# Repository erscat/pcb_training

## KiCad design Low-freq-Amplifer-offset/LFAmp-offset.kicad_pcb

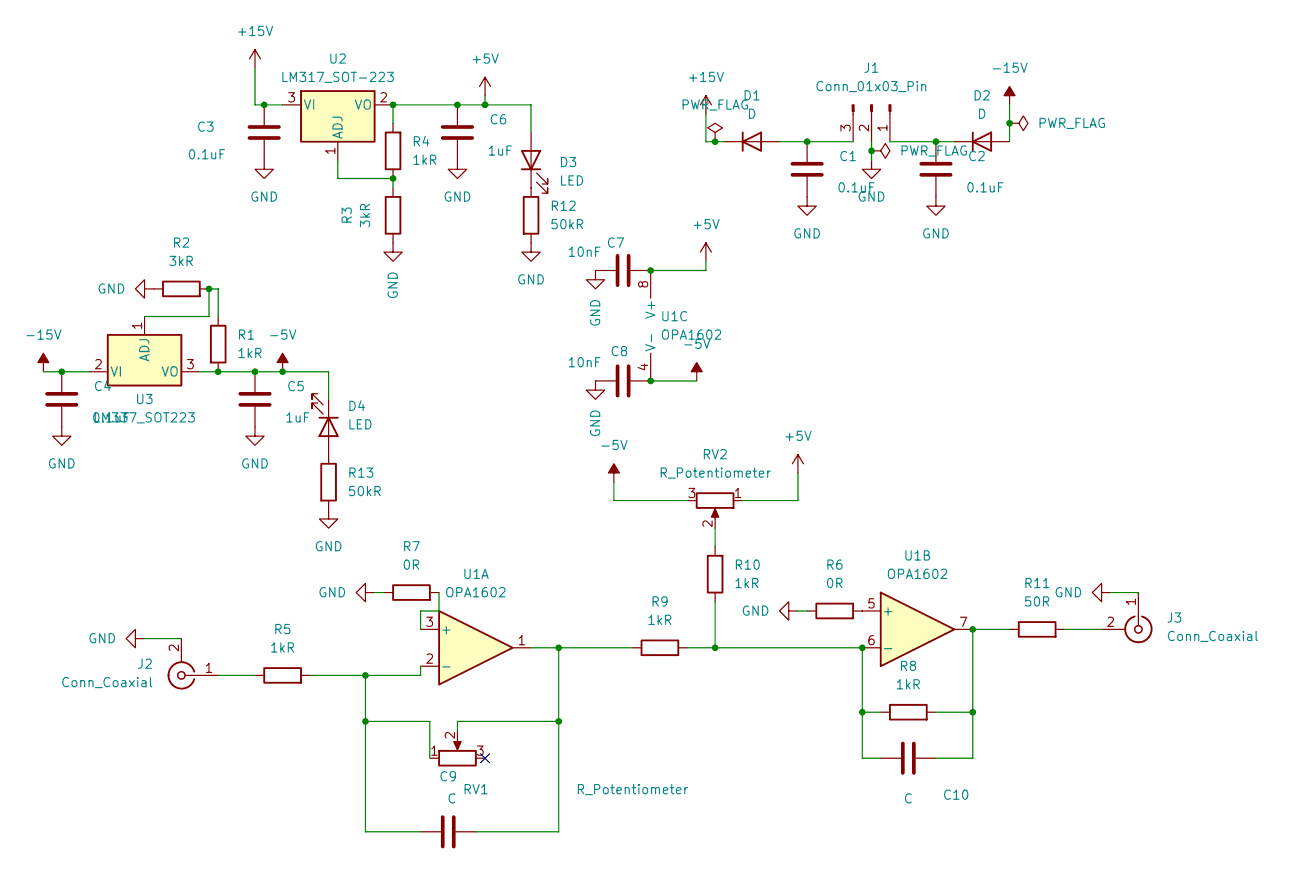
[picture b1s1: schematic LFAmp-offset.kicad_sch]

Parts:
C1, C2, C3, C4: 0.1uF; C_1206_3216Metric
C5, C6: 1uF; C_1206_3216Metric
C7, C8: 10nF; C_1206_3216Metric
C9, C10: C; C_1206_3216Metric
D1, D2: D; D_1206_3216Metric
D3, D4: LED; D_1206_3216Metric
J1: Conn_01x03_Pin; PinSocket_1x03_P2.54mm_Vertical
J2, J3: Conn_Coaxial; SMA_Amphenol_132289_EdgeMount
R1, R4, R5, R8, R9, R10: 1kR; R_1206_3216Metric
R2, R3: 3kR; R_1206_3216Metric
R6, R7: 0R; R_1206_3216Metric
R11: 50R; R_1206_3216Metric
R12, R13: 50kR; R_1206_3216Metric
RV1, RV2: R_Potentiometer; PinSocket_1x03_P2.54mm_Vertical
U1: OPA1602; SOIC-8-1EP_3.9x4.9mm_P1.27mm_EP2.29x3mm
U2: LM317_SOT-223; SOT-223-3_TabPin2
U3: LM337_SOT223; SOT-223-3_TabPin2

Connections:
+5V: C6.1, C7.1, D3.2 (A), R4.2, RV2.1, U1.8 (V+), U2.2 (VO)
+15V: C3.1, D1.1 (K), U2.3 (VI)
-5V: C5.1, C8.1, D4.1 (K), R1.2, RV2.3, U1.4 (V-), U3.3 (VO)
-15V: C4.1, D2.2 (A), U3.2 (VI)
GND: C1.2, C2.2, C3.2, C4.2, C5.2, C6.2, C7.2, C8.2, J1.2, J2.2 (Ext), J3.1 (In), R2.1, R3.1, R6.1, R7.1, R12.2, R13.2
unnamed: C9.2, R9.1, RV1.2, U1.1
unnamed: C10.2, R8.2, R11.1, U1.7
unnamed: C1.1, D1.2 (A), J1.3
unnamed: C2.1, D2.1 (K), J1.1
unnamed: D3.1 (K), R12.1
unnamed: D4.2 (A), R13.1
unnamed: J2.1 (In), R5.1
unnamed: J3.2 (Ext), R11.2
unnamed: R10.2, RV2.2
unnamed: R7.2, U1.3 (+)
unnamed: C9.1, R5.2, RV1.1, U1.2 (-)
unnamed: R6.2, U1.5 (+)
unnamed: C10.1, R8.1, R9.2, R10.1, U1.6 (-)
unnamed: R3.2, R4.1, U2.1 (ADJ)
unnamed: R1.1, R2.2, U3.1 (ADJ)

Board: 2 copper layers, 35 parts (0 on the bottom side), 20 nets, no tracks yet.

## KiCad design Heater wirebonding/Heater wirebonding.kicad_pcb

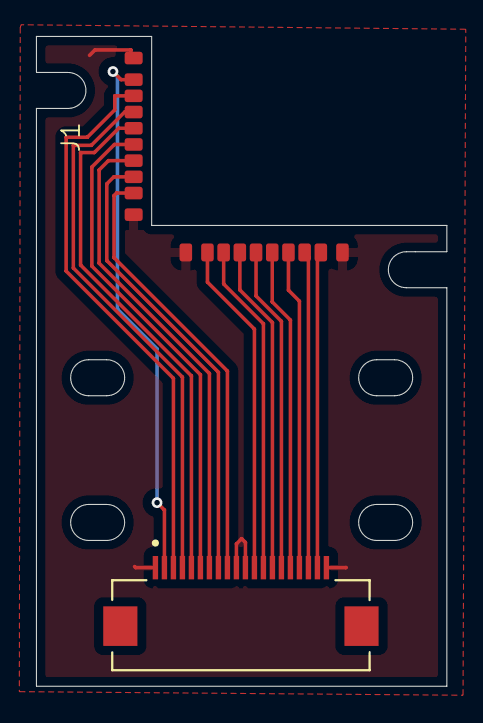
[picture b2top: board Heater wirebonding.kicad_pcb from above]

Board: 2 copper layers, 22.8 x 36.1 mm, 3 parts (0 on the bottom side), 17 nets.

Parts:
J1, J3: Conn_01x10_Pin; Pads 1x10
J2: TF31-20S-0.5SH_800_; HRS_TF31-20S-0.5SH_800_

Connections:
GND: J1.1, J1.10, J2.1, J2.10, J2.11, J2.20, J3.1, J3.10
unnamed: J1.2, J2.9
unnamed: J1.3, J2.8
unnamed: J1.4, J2.7
unnamed: J1.5, J2.6
unnamed: J1.6, J2.5
unnamed: J1.7, J2.4
unnamed: J1.8, J2.3
unnamed: J1.9, J2.2
unnamed: J2.19, J3.2
unnamed: J2.18, J3.3
unnamed: J2.17, J3.4
unnamed: J2.16, J3.5
unnamed: J2.15, J3.6
unnamed: J2.14, J3.7
unnamed: J2.13, J3.8
unnamed: J2.12, J3.9

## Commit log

2025-11-05 Files from Meeting on 29-10-25
2025-11-05 diodes are introduced
2025-11-11 Modified PCB layout to account for screw head
2025-11-12 Create README.md
    Create the project
2025-11-14 Modified PCB design
    Changed 4 wirebond pads to ground and filled in PCB GND zone. Changed PCB shape such that the PCB acts as the clamp for the chip.
